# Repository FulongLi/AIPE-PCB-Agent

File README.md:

# AIPE — PCB Agent

AIPE-PCB-Agent is the PCB design automation of the AIPE power-electronics ecosystem. Python generators turn a
requirement file set (specification, insulation table, components, interfaces, floorplan and routing inputs) into
native KiCad 10 projects — hierarchical schematics, placed and grid-routed boards, net classes and design rules —
and run the real `kicad-cli` ERC, DRC and exports with SHA-256 manifests. It sits downstream of
AIPE-Electrical-Design in the AIPE-Workflows pipeline. Its output is an AI-generated engineering prototype for human
review: nothing has been fabricated, energised or measured.

## Features

- Requirement-driven generators (`automation/dab_v1`, `automation/sic_v3`, `automation/kicad_tools`): schematics with
  project libraries, insulation-aware placement, a deterministic grid router with fine-pitch row escapes, pour nets,
  rip-up, time budget and checkpoints.
- Net classes and `.kicad_dru` rules derived from an IEC 60664-1 reference table; values are documented review inputs
  and are never relaxed by the code.
- Native verification: `kicad-cli sch erc`, `pcb drc --schematic-parity --severity-all --refill-zones`, exports
  (Gerber, drill, BOM, placement, STEP, PDF, netlist) with hashed manifests; netlist-equality, routing-quality,
  layout-metric and copper-island checkers.
- Engineering knowledge base (skills, rules, component records) with traceable manufacturer sources.
- Worked examples: SiC buck V1–V3 and the 10 kW dual-active-bridge three-board set DAB-V1.

## Installation

```text
python -m pip install -e ".[test]"          # Python 3.10+; numpy, PyYAML, Shapely, pytest
python -m automation.setup.detect_kicad    # locates an installed KiCad 10 (kicad-cli and its Python); installs nothing
```

## Usage

```text
python -m pytest -q
python -m automation.knowledge.query "recommended layout practices for an isolated SiC gate driver"
python -m automation.dab_v1.pipeline --board primary-power --stages floorplan,copper,route,verify --time-budget 2700
```

The tests run without KiCad (KiCad-dependent tests skip and say so); the pipeline's board stages need KiCad 10.
`--time-budget` time-boxes the router: unrouted nets are reported, the board is still saved and verified.

## Project Information

- Version: 0.1.0 (`pyproject.toml`; first declared version, aligned with `aipe.yaml` schema 0.1.0)
- Status: Prototype. SiC buck V3: two routed boards at zero native ERC/DRC findings. DAB-V1 (re-run of 2026-10-21):
  ERC 0 on all three boards, DRC 0 violations other than unconnected items (18 / 18 / 28 dangling-track warnings),
  26 / 23 / 24 connections still open on primary / secondary / control (from 82 / 81 / 499) - routing candidates, not
  finished boards. No board has been fabricated.
- Developer: Fulong Li
- Organisation: Spirit Connect / AIPE Labs
- License: code — MIT is declared in `aipe.yaml`, but the repository contains no LICENSE file yet (the licence text has
  to be added by the maintainer); KiCad library data under `examples/*/libraries` — CC-BY-SA-4.0 with the KiCad
  library exception (`examples/dab-10kw/control/libraries/LICENSE.md`).

## Documentation

- [Automation architecture](docs/architecture.md), [workflow and acceptance gates](docs/agent-workflow.md),
  [PCB design rules](docs/pcb-design-rules.md), [knowledge system](docs/knowledge-system.md)
- DAB-V1: [example README](examples/dab-10kw/README.md), [architecture review](docs/dab-10kw/architecture-review.md),
  [review report](docs/dab-10kw/review-report.md), [routing remediation](docs/dab-10kw/routing-remediation.md)
- SiC buck examples and milestone history (former README): [docs/history.md](docs/history.md),
  [V3 package](examples/sic-buck-400v-200v-5kw-v3/README.md)
- [Host environment](docs/environment.md), [installation plan](docs/installation-plan.md),
  [CI workflow](.github/workflows/tests.yml)

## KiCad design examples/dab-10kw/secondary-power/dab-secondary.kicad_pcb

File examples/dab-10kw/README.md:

# AIPE 10 kW dual active bridge - DAB-V1 (800 V / 400 V, 100 kHz, SPS)

**AI-GENERATED ENGINEERING PROTOTYPE - HUMAN REVIEW REQUIRED - NOT HARDWARE QUALIFIED.** Three native KiCad 10
projects generated by `automation/dab_v1` from the requirement files in `requirements/`. Clean ERC/DRC results are CAD
statements about the generated files under the recorded rule set; they establish neither electrical safety nor
manufacturability. No fabrication, procurement or energisation is authorised by anything in this directory.

| Deliverable | Location |
|---|---|
| Requirements, assumptions, insulation table, interfaces, floorplans, routing inputs | `requirements/*.yaml`, provenance `requirements/source_manifest.json` |
| Safety-oriented architecture review | [`docs/dab-10kw/architecture-review.md`](../../docs/dab-10kw/architecture-review.md) |
| Review report (what clean ERC/DRC does and does not mean; reviewer checklist) | [`docs/dab-10kw/review-report.md`](../../docs/dab-10kw/review-report.md) |
| Primary power board (800 V bus) | `primary-power/dab-primary.kicad_pro` (schematic `dab-primary.kicad_sch`, board `dab-primary.kicad_pcb`, rules `dab-primary.kicad_dru`, libraries `libraries/`) |
| Secondary power board (400 V bus) | `secondary-power/dab-secondary.kicad_pro` |
| Control board (TMS320F280039C controlCARD) | `control/dab-control.kicad_pro` |
| Design records (evaluated models, groups, spacing evidence, library summaries, schematic mappings) | `design/` |
| Placement and copper plans, routing plans and router reports | `pcb/floorplan_<board>.json`, `pcb/routing_plan_<board>.json`, `pcb/routing_report_<board>.json` |
| Native ERC / DRC manifests (every run, hashed) | `verification/erc/<stamp>/run.json`, `verification/drc/<stamp>/run.json` |
| Netlist equality, routing quality, layout metrics, copper islands, per-board summaries | `verification/circuit_checks/`, `verification/engineering_checks/`, `verification/summary_<board>.json` |
| Manufacturing exports with hashed manifests (Gerbers, drill, BOM, pick-and-place, STEP, PDFs, renders, XML netlist) | `manufacturing/<board>/` |
| Model BOMs | `components/bom_<board>.csv` |

## Reproduction

Host Python 3.10+ (PyYAML optional) and KiCad 10 (kicad-cli and its bundled Python, found by `automation.setup.detect_kicad`).

```text
python -m automation.dab_v1.schematics --board primary-power --erc       # libraries, hierarchical schematic, rules, ERC
<KiCad python> -m automation.dab_v1.floorplan --board primary-power      # placement, copper plan and fine-pitch row escapes (pcbnew)
python -m automation.dab_v1.copper --board primary-power                 # merge the pour rectangles (Shapely)
<KiCad python> -m automation.dab_v1.routing --board primary-power --time-budget 2700   # grid_router.run_plan through PairwiseRouter
python -m automation.dab_v1.verify --board primary-power                 # DRC, exports, netlist equality, quality, layout, islands
python -m automation.dab_v1.pipeline --board primary-power --time-budget 2700          # the stages in sequence
python -m automation.dab_v1.report                                       # refresh the result tables of docs/dab-10kw/review-report.md
python -m automation.dab_v1.provenance                                   # re-fetch and hash the manufacturer sources
python -m pytest tests/test_dab_v1.py -q
```

Repeat with `secondary-power` and `control`. Regeneration reproduces the schematic bytes and the placement; routed
copper is reproduced item for item but not byte for byte (random KiCad item ids), so compare geometry and the hashed
manifests, not file bytes. `--time-budget` (seconds) time-boxes the router: nets it did not reach are recorded as
unresolved with `reason: time_budget`, the board is still poured, filled and saved, and a checkpoint board is written
under `.aipe/dab/checkpoints/` after every router stage. The escape plan of the 0.65 mm rows (same-net bridges, one stub
per run, computed stub lengths) is recorded per IC in `pcb/floorplan_<board>.json -> plan.escape_rows`; see
[`docs/dab-10kw/routing-remediation.md`](../../docs/dab-10kw/routing-remediation.md) for the root causes it addresses.

## What is in the requirement files

- `specification.yaml` - user requirements, engineering assumptions, derived operating point, unverified design
  targets, verification policy.
- `design_constraints.yaml` - stack-ups, minimum features, the IEC 60664-1 reference table (clearance by impulse,
  creepage PD2 MG I, interpolated functional spacing, 8.0 mm reinforced HV-to-SELV), the potential model of the HV
  domains and the router defaults.
- `components.yaml` - every part selection with manufacturer source and the verification level of its pin table or
  envelope.
- `interfaces.yaml` - the 40-way harness map (identical on all three boards), the assumed controlCARD contact map,
  JTAG, CAN, RS-485, auxiliary input, heat-sink NTC and HV terminals.
- `floorplan_<board>.yaml`, `routing_<board>.yaml` - placement geometry and router parameters.

## Status (2026-10-21, remediation run - see `docs/dab-10kw/routing-remediation.md`)

| Board | ERC | Routing | Native DRC (`--schematic-parity --severity-all --refill-zones`) | Exports |
|---|---|---|---|---|
| primary-power | 0 findings | grid router: 2501 tracks, 436 vias, 22 pours, **26 connections left open** (1161 s, time budget not reached) | **0 violations other than unconnected items** (18 dangling-track warnings), **26 unconnected items in 18 nets**, parity 0 | 11 commands, 36 artifacts, hashed |
| secondary-power | 0 findings | 2598 tracks, 449 vias, 21 pours, **23 connections left open** (1189 s) | **0 violations other than unconnected items** (18 dangling-track warnings), **23 unconnected items in 16 nets**, parity 0 | 11 commands, 36 artifacts, hashed |
| control | 0 findings | 3090 tracks, 622 vias, 1 pour, **24 connections left open** (2714 s; the 45-minute budget was reached after one signal trial, rip-up and retry were cut) | **0 violations other than unconnected items** (28 dangling-track warnings), **24 unconnected items in 23 nets**, parity 0 | 11 commands, 36 artifacts, hashed |

Model / schematic netlist / board pad-net equality is exact on all three boards; every power and ground pour is a
single filled island on both power boards; the 8.0 mm HV-to-SELV separation holds on every copper layer and across the
stack (`verification/engineering_checks/barrier_geometry_<board>.json`). The open connections of the power boards are
the narrow nets of the UCC14141 rows (BIAS_ENF, PG_BIAS_N, FBVEE/FBVDD/VEEA/RLIM) and a few island nets; they are listed
per net in `verification/summary_<board>.json` and in the review report. **These are routing candidates, not finished
boards: no Gerber set is manufacturing-ready while connections are open.**

See `docs/dab-10kw/review-report.md` for the per-board ERC/DRC counts, ignored checks, export lists, remaining
violations and the open review items. The controlCARD contact map, several transcribed pin tables, the film-capacitor
and heat-sink envelopes and every insulation value are review inputs, not verified facts.

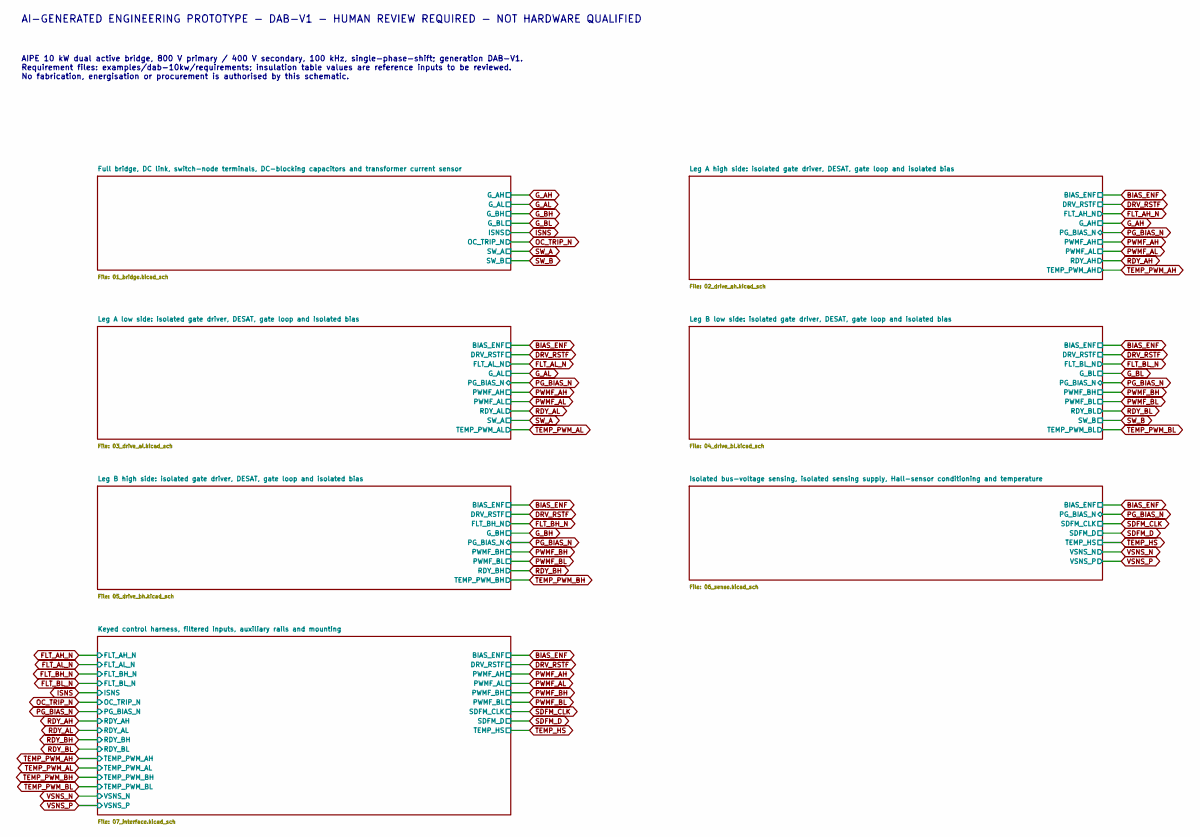
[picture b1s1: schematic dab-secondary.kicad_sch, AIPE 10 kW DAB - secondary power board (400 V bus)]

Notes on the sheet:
AI-GENERATED ENGINEERING PROTOTYPE - DAB-V1 - HUMAN REVIEW REQUIRED - NOT HARDWARE QUALIFIED
AIPE 10 kW dual active bridge, 800 V primary / 400 V secondary, 100 kHz, single-phase-shift; generation DAB-V1. Requirement files: examples/dab-10kw/requirements; insulation table values are reference inputs to be reviewed. No fabrication, energisation or procurement is authorised by this schematic.

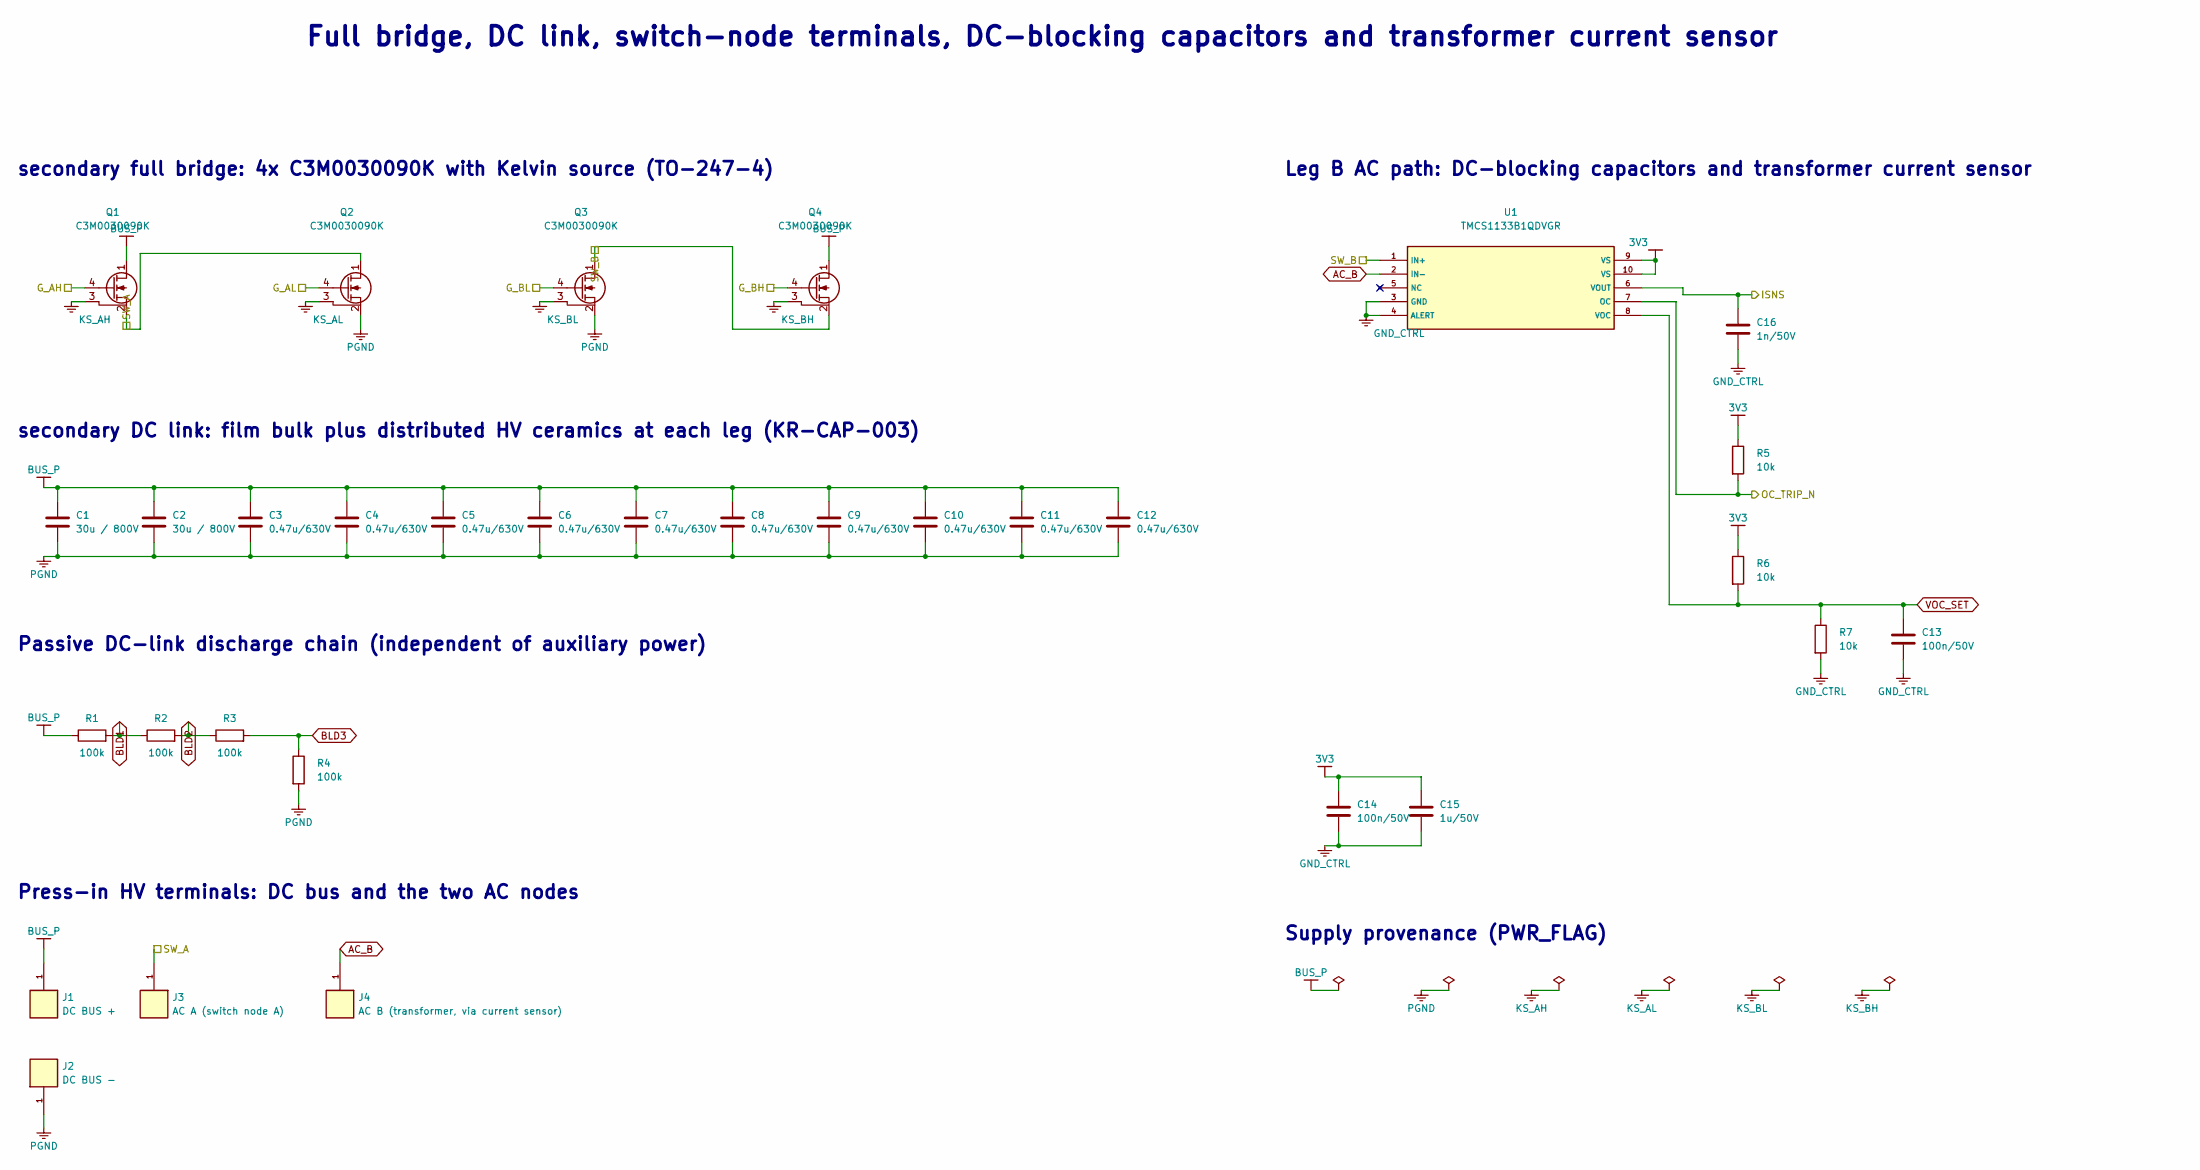
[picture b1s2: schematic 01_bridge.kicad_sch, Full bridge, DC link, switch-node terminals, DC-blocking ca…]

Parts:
C1, C2: 30u / 800V; DAB_FILM_SECONDARY
C3, C4, C5, C6, C7, C8, C9, C10, C11, C12: 0.47u/630V; C_2220_5750Metric
C13, C14: 100n/50V; C_0603_1608Metric
C15: 1u/50V; C_0805_2012Metric
C16: 1n/50V; C_0603_1608Metric
J1: DC BUS +; Wuerth_REDCUBE-THR_WP-THRSH_74651195_THR
J2: DC BUS -; Wuerth_REDCUBE-THR_WP-THRSH_74651195_THR
J3: AC A (switch node A); Wuerth_REDCUBE-THR_WP-THRSH_74651195_THR
J4: AC B (transformer, via current sensor); Wuerth_REDCUBE-THR_WP-THRSH_74651195_THR
Q1, Q2, Q3, Q4: C3M0030090K; TO-247-4_Vertical
R1, R2, R3, R4: 100k; R_1210_3225Metric
R5, R6, R7: 10k; R_0603_1608Metric
U1: TMCS1133B1QDVGR; DAB_TMCS1133_DVG

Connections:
3V3: C14.1, C15.1, R5.1, R6.1, U1.9 (VS), U1.10 (VS); also elsewhere on the board
AC_B: J4.1, U1.2 (IN-)
BLD1: R1.2, R2.1
BLD2: R2.2, R3.1
BLD3: R3.2, R4.1
BUS_P: C1.1, C2.1, C3.1, C4.1, C5.1, C6.1, C7.1, C8.1, C9.1, C10.1, C11.1, C12.1, J1.1, Q1.1 (D), Q4.1 (D), R1.1; also elsewhere on the board
GND_CTRL: C13.2, C14.2, C15.2, C16.2, R7.2, U1.3 (GND), U1.4 (ALERT); also elsewhere on the board
G_AH: Q1.4 (G); also elsewhere on the board
G_AL: Q2.4 (G); also elsewhere on the board
G_BH: Q4.4 (G); also elsewhere on the board
G_BL: Q3.4 (G); also elsewhere on the board
ISNS: C16.1, U1.6 (VOUT); also elsewhere on the board
KS_AH: Q1.3 (KS); also elsewhere on the board
KS_AL: Q2.3 (KS); also elsewhere on the board
KS_BH: Q4.3 (KS); also elsewhere on the board
KS_BL: Q3.3 (KS); also elsewhere on the board
OC_TRIP_N: R5.2, U1.7 (OC); also elsewhere on the board
PGND: C1.2, C2.2, C3.2, C4.2, C5.2, C6.2, C7.2, C8.2, C9.2, C10.2, C11.2, C12.2, J2.1, Q2.2 (S), Q3.2 (S), R4.2; also elsewhere on the board
SW_A: J3.1, Q1.2 (S), Q2.1 (D); also elsewhere on the board
SW_B: Q3.1 (D), Q4.2 (S), U1.1 (IN+); also elsewhere on the board
VOC_SET: C13.1, R6.2, R7.1, U1.8 (VOC)

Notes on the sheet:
Full bridge, DC link, switch-node terminals, DC-blocking capacitors and transformer current sensor
secondary full bridge: 4x C3M0030090K with Kelvin source (TO-247-4)
secondary DC link: film bulk plus distributed HV ceramics at each leg (KR-CAP-003)
Passive DC-link discharge chain (independent of auxiliary power)
Press-in HV terminals: DC bus and the two AC nodes
Leg B AC path: DC-blocking capacitors and transformer current sensor
Supply provenance (PWR_FLAG)

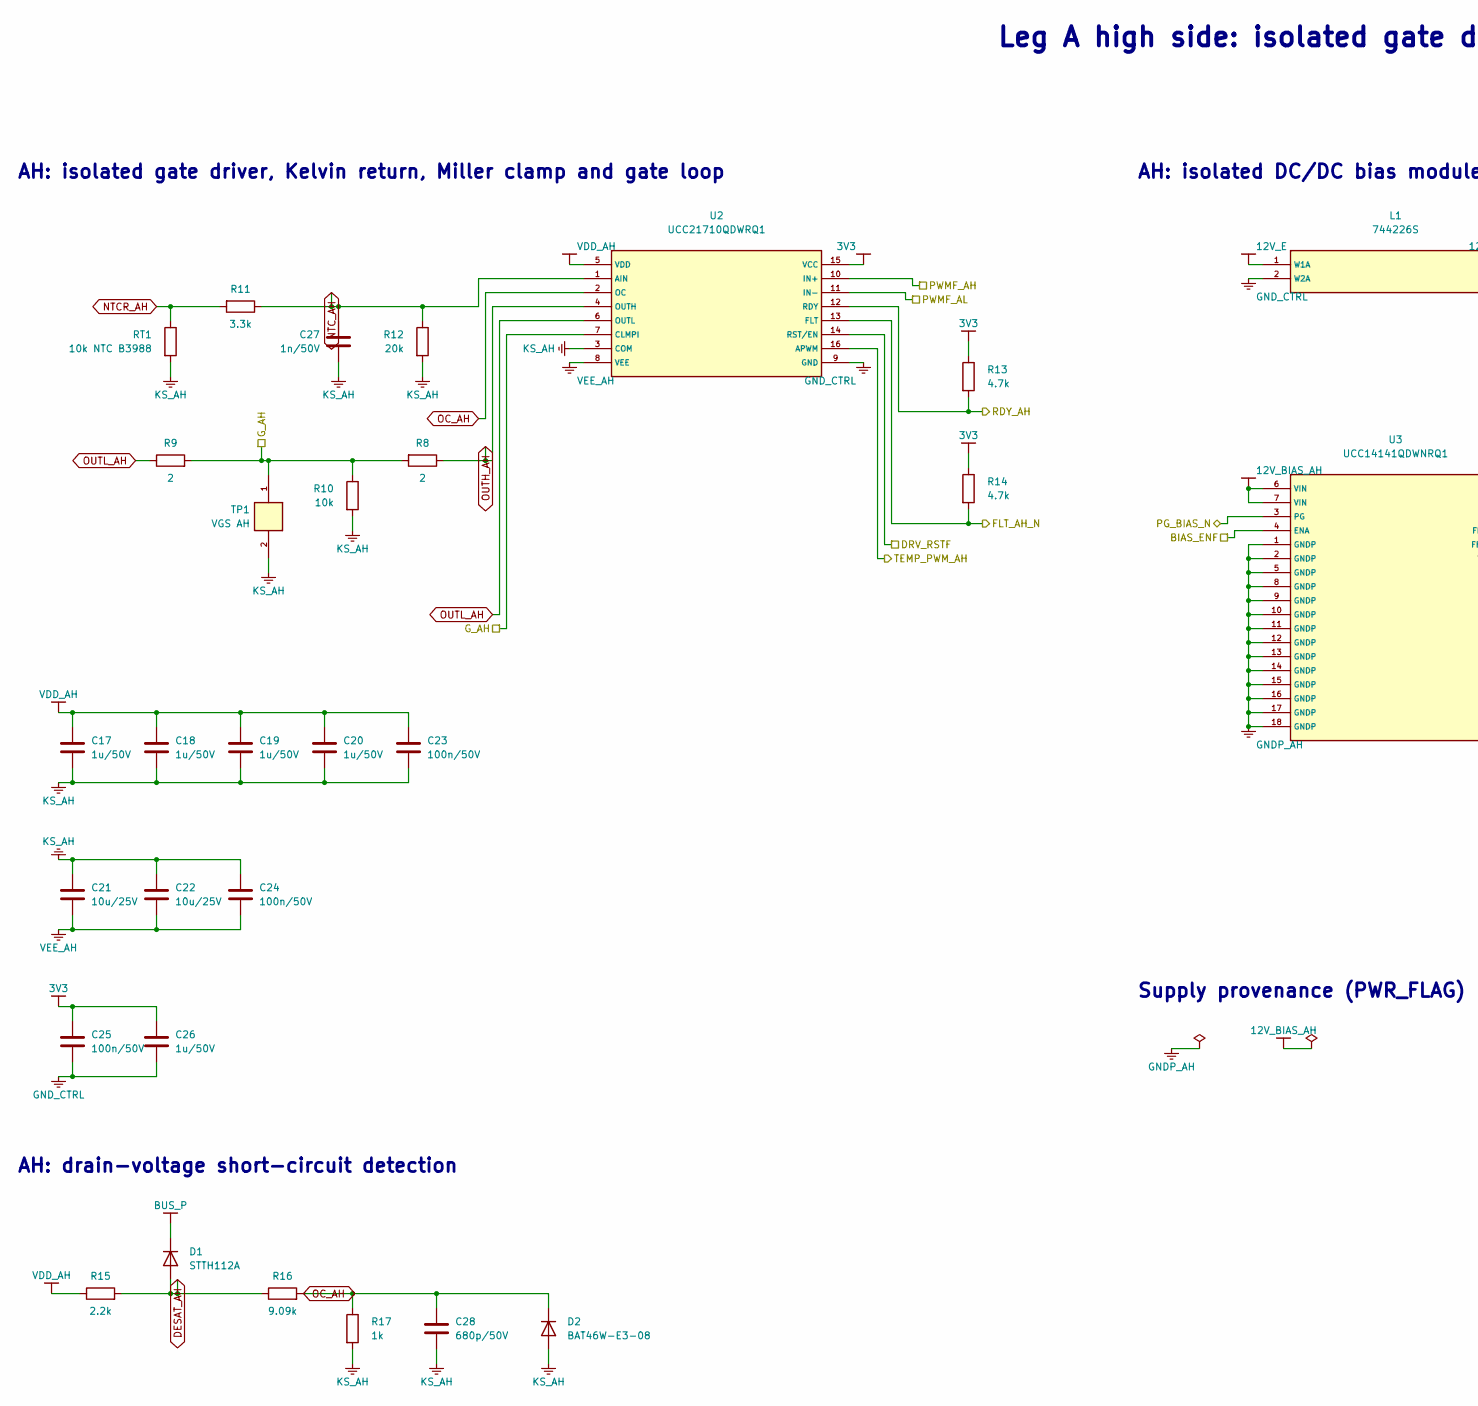
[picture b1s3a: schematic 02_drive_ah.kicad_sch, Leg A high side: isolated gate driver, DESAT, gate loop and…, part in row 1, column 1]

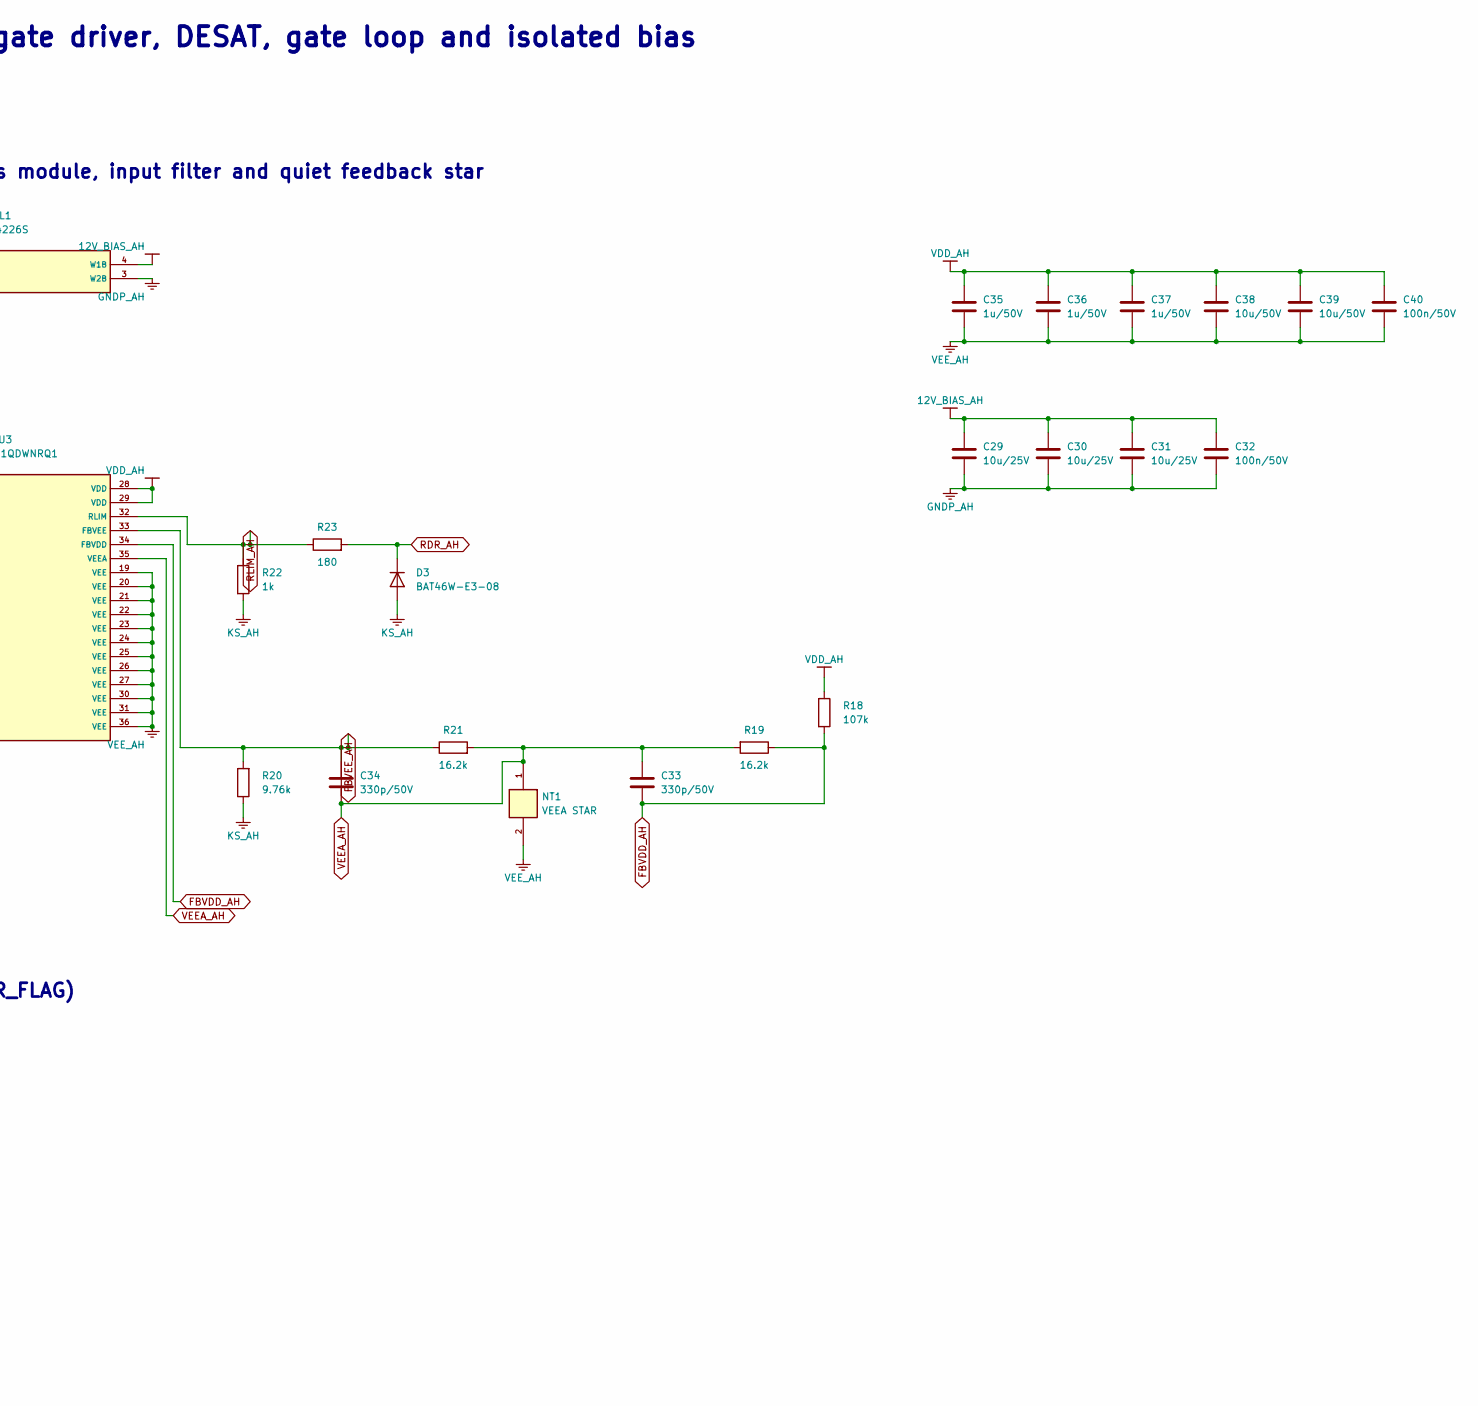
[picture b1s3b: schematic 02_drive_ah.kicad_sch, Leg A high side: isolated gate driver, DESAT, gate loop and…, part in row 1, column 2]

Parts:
C17, C18, C19, C20, C26, C35, C36, C37: 1u/50V; C_0805_2012Metric
C21, C22, C29, C30, C31: 10u/25V; C_1210_3225Metric
C23, C24, C25, C32, C40: 100n/50V; C_0603_1608Metric
C27: 1n/50V; C_0603_1608Metric
C28: 680p/50V; C_0603_1608Metric
C33, C34: 330p/50V; C_0603_1608Metric
C38, C39: 10u/50V; C_1210_3225Metric
D1: STTH112A; D_DO-41_SOD81_P10.16mm_Horizontal
D2, D3: BAT46W-E3-08; D_SOD-123
L1: 744226S; L_CommonMode_Wuerth_WE-SL2
NT1: VEEA STAR; NetTie-2_SMD_Pad0.5mm
R8, R9: 2; R_1206_3216Metric
R10: 10k; R_0805_2012Metric
R11: 3.3k; R_0603_1608Metric
R12: 20k; R_0603_1608Metric
R13, R14: 4.7k; R_0603_1608Metric
R15: 2.2k; R_1206_3216Metric
R16: 9.09k; R_0603_1608Metric
R17: 1k; R_0603_1608Metric
R18: 107k; R_0603_1608Metric
R19, R21: 16.2k; R_0603_1608Metric
R20: 9.76k; R_0603_1608Metric
R22: 1k; R_1206_3216Metric
R23: 180; R_1206_3216Metric
RT1: 10k NTC B3988; R_0805_2012Metric
TP1: VGS AH; TestPoint_2Pads_Pitch2.54mm_Drill0.8mm
U2: UCC21710QDWRQ1; DAB_UCC21710_DW_HV
U3: UCC14141QDWNRQ1; DAB_UCC14141_DWN

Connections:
3V3: C25.1, C26.1, R13.1, R14.1, U2.15 (VCC); also elsewhere on the board
12V_BIAS_AH: C29.1, C30.1, C31.1, C32.1, L1.4 (W1B), U3.6 (VIN), U3.7 (VIN)
12V_E: L1.1 (W1A); also elsewhere on the board
BIAS_ENF: U3.4 (ENA); also elsewhere on the board
BUS_P: D1.1 (K); also elsewhere on the board
DESAT_AH: D1.2 (A), R15.2, R16.1
DRV_RSTF: U2.14 (RST/EN); also elsewhere on the board
FBVDD_AH: C33.1, R18.2, R19.1, U3.34 (FBVDD)
FBVEE_AH: C34.1, R20.2, R21.1, U3.33 (FBVEE)
FLT_AH_N: R14.2, U2.13 (FLT); also elsewhere on the board
GNDP_AH: C29.2, C30.2, C31.2, C32.2, L1.3 (W2B), U3.1 (GNDP), U3.2 (GNDP), U3.5 (GNDP), U3.8 (GNDP), U3.9 (GNDP), U3.10 (GNDP), U3.11 (GNDP), U3.12 (GNDP), U3.13 (GNDP), U3.14 (GNDP), U3.15 (GNDP), U3.16 (GNDP), U3.17 (GNDP), U3.18 (GNDP)
GND_CTRL: C25.2, C26.2, L1.2 (W2A), U2.9 (GND); also elsewhere on the board
G_AH: R8.2, R9.2, R10.1, TP1.1, U2.7 (CLMPI); also elsewhere on the board
KS_AH: C17.2, C18.2, C19.2, C20.2, C21.1, C22.1, C23.2, C24.1, C27.2, C28.2, D2.2 (A), D3.2 (A), R10.2, R12.2, R17.2, R20.1, R22.2, RT1.2, TP1.2, U2.3 (COM); also elsewhere on the board
NTCR_AH: R11.2, RT1.1
NTC_AH: C27.1, R11.1, R12.1, U2.1 (AIN)
OC_AH: C28.1, D2.1 (K), R16.2, R17.1, U2.2 (OC)
OUTH_AH: R8.1, U2.4 (OUTH)
OUTL_AH: R9.1, U2.6 (OUTL)
PG_BIAS_N: U3.3 (PG); also elsewhere on the board
PWMF_AH: U2.10 (IN+); also elsewhere on the board
PWMF_AL: U2.11 (IN-); also elsewhere on the board
RDR_AH: D3.1 (K), R23.2
RDY_AH: R13.2, U2.12 (RDY); also elsewhere on the board
RLIM_AH: R22.1, R23.1, U3.32 (RLIM)
TEMP_PWM_AH: U2.16 (APWM); also elsewhere on the board
VDD_AH: C17.1, C18.1, C19.1, C20.1, C23.1, C35.1, C36.1, C37.1, C38.1, C39.1, C40.1, R15.1, R18.1, U2.5 (VDD), U3.28 (VDD), U3.29 (VDD)
VEEA_AH: C33.2, C34.2, NT1.1, R19.2, R21.2, U3.35 (VEEA)
VEE_AH: C21.2, C22.2, C24.2, C35.2, C36.2, C37.2, C38.2, C39.2, C40.2, NT1.2, U2.8 (VEE), U3.19 (VEE), U3.20 (VEE), U3.21 (VEE), U3.22 (VEE), U3.23 (VEE), U3.24 (VEE), U3.25 (VEE), U3.26 (VEE), U3.27 (VEE), U3.30 (VEE), U3.31 (VEE), U3.36 (VEE)

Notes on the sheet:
Leg A high side: isolated gate driver, DESAT, gate loop and isolated bias
AH: isolated gate driver, Kelvin return, Miller clamp and gate loop
AH: drain-voltage short-circuit detection
AH: isolated DC/DC bias module, input filter and quiet feedback star
Supply provenance (PWR_FLAG)

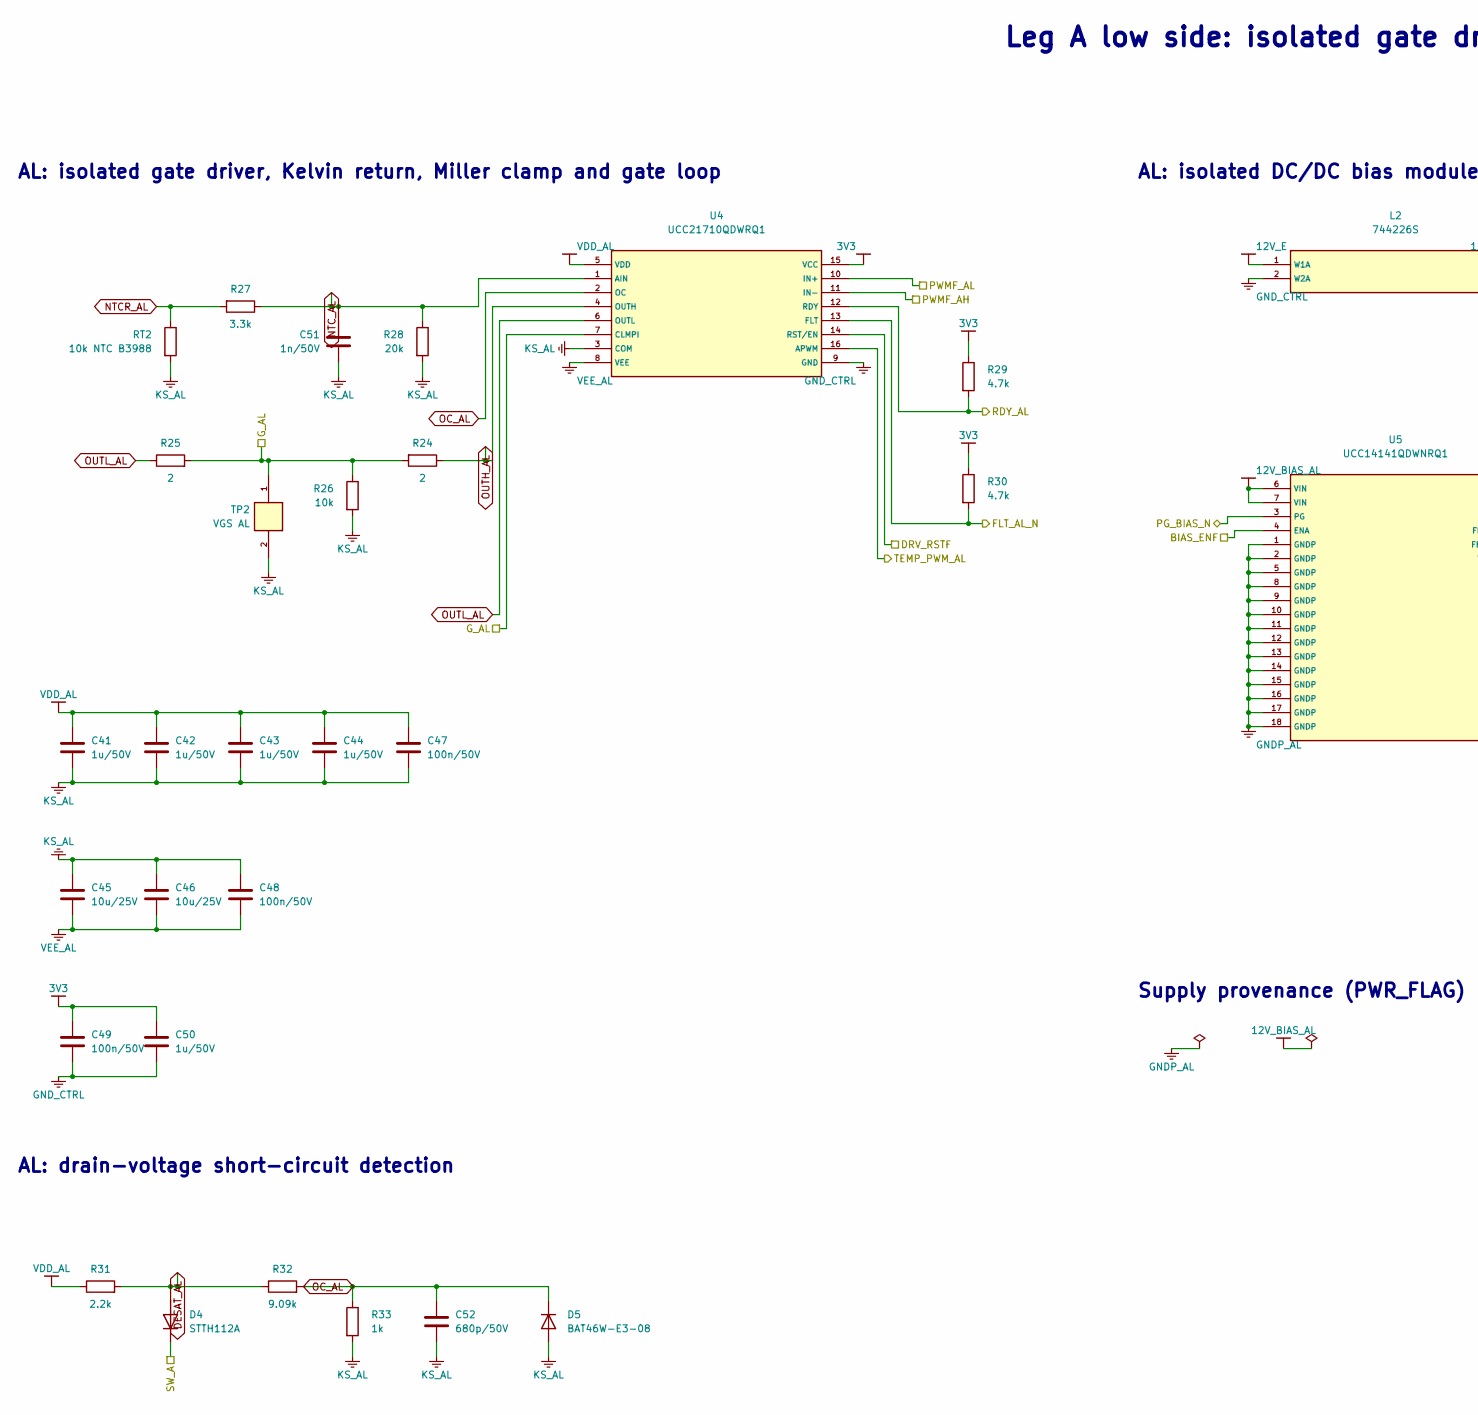
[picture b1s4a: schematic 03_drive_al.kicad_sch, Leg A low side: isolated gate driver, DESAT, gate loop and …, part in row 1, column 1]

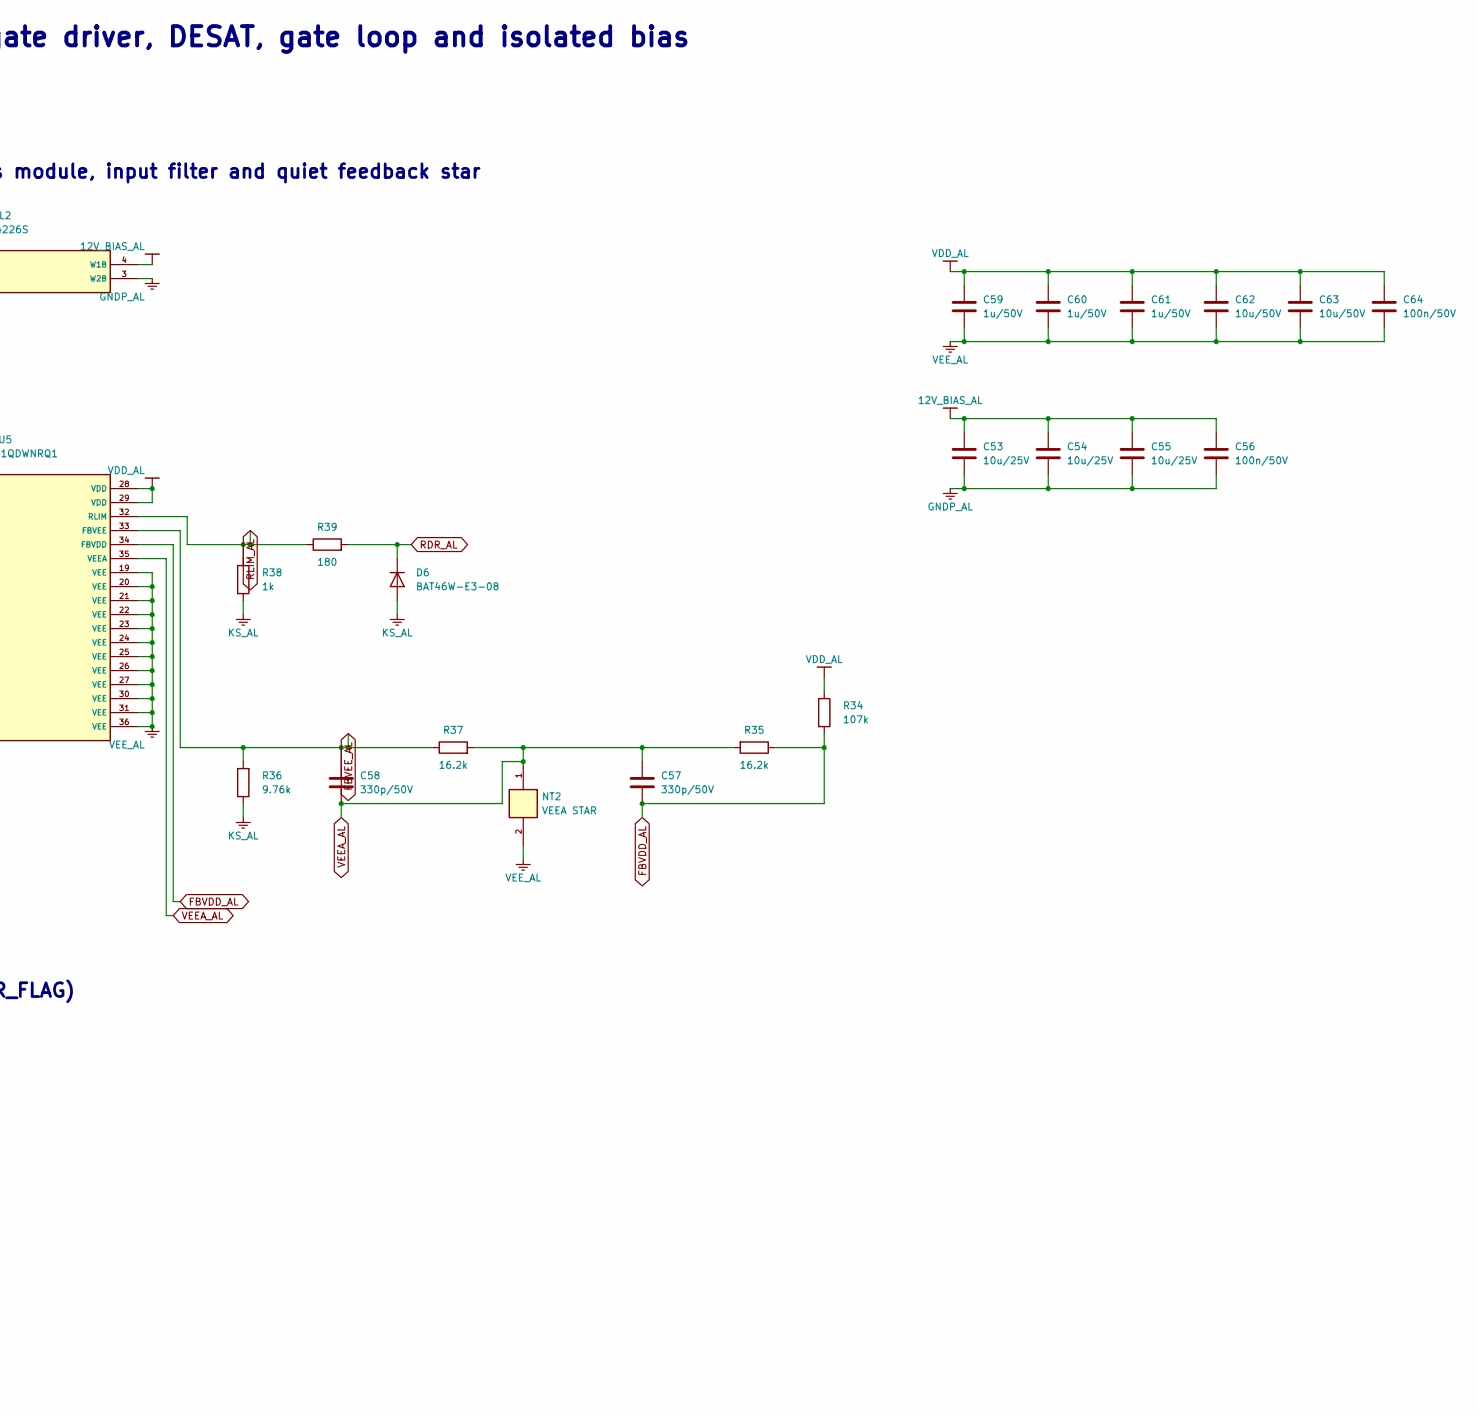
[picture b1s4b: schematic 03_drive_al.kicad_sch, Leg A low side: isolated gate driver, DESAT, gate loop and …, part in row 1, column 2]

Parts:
C41, C42, C43, C44, C50, C59, C60, C61: 1u/50V; C_0805_2012Metric
C45, C46, C53, C54, C55: 10u/25V; C_1210_3225Metric
C47, C48, C49, C56, C64: 100n/50V; C_0603_1608Metric
C51: 1n/50V; C_0603_1608Metric
C52: 680p/50V; C_0603_1608Metric
C57, C58: 330p/50V; C_0603_1608Metric
C62, C63: 10u/50V; C_1210_3225Metric
D4: STTH112A; D_DO-41_SOD81_P10.16mm_Horizontal
D5, D6: BAT46W-E3-08; D_SOD-123
L2: 744226S; L_CommonMode_Wuerth_WE-SL2
NT2: VEEA STAR; NetTie-2_SMD_Pad0.5mm
R24, R25: 2; R_1206_3216Metric
R26: 10k; R_0805_2012Metric
R27: 3.3k; R_0603_1608Metric
R28: 20k; R_0603_1608Metric
R29, R30: 4.7k; R_0603_1608Metric
R31: 2.2k; R_1206_3216Metric
R32: 9.09k; R_0603_1608Metric
R33: 1k; R_0603_1608Metric
R34: 107k; R_0603_1608Metric
R35, R37: 16.2k; R_0603_1608Metric
R36: 9.76k; R_0603_1608Metric
R38: 1k; R_1206_3216Metric
R39: 180; R_1206_3216Metric
RT2: 10k NTC B3988; R_0805_2012Metric
TP2: VGS AL; TestPoint_2Pads_Pitch2.54mm_Drill0.8mm
U4: UCC21710QDWRQ1; DAB_UCC21710_DW_HV
U5: UCC14141QDWNRQ1; DAB_UCC14141_DWN

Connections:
3V3: C49.1, C50.1, R29.1, R30.1, U4.15 (VCC); also elsewhere on the board
12V_BIAS_AL: C53.1, C54.1, C55.1, C56.1, L2.4 (W1B), U5.6 (VIN), U5.7 (VIN)
12V_E: L2.1 (W1A); also elsewhere on the board
BIAS_ENF: U5.4 (ENA); also elsewhere on the board
DESAT_AL: D4.2 (A), R31.2, R32.1
DRV_RSTF: U4.14 (RST/EN); also elsewhere on the board
FBVDD_AL: C57.1, R34.2, R35.1, U5.34 (FBVDD)
FBVEE_AL: C58.1, R36.2, R37.1, U5.33 (FBVEE)
FLT_AL_N: R30.2, U4.13 (FLT); also elsewhere on the board
GNDP_AL: C53.2, C54.2, C55.2, C56.2, L2.3 (W2B), U5.1 (GNDP), U5.2 (GNDP), U5.5 (GNDP), U5.8 (GNDP), U5.9 (GNDP), U5.10 (GNDP), U5.11 (GNDP), U5.12 (GNDP), U5.13 (GNDP), U5.14 (GNDP), U5.15 (GNDP), U5.16 (GNDP), U5.17 (GNDP), U5.18 (GNDP)
GND_CTRL: C49.2, C50.2, L2.2 (W2A), U4.9 (GND); also elsewhere on the board
G_AL: R24.2, R25.2, R26.1, TP2.1, U4.7 (CLMPI); also elsewhere on the board
KS_AL: C41.2, C42.2, C43.2, C44.2, C45.1, C46.1, C47.2, C48.1, C51.2, C52.2, D5.2 (A), D6.2 (A), R26.2, R28.2, R33.2, R36.1, R38.2, RT2.2, TP2.2, U4.3 (COM); also elsewhere on the board
NTCR_AL: R27.2, RT2.1
NTC_AL: C51.1, R27.1, R28.1, U4.1 (AIN)
OC_AL: C52.1, D5.1 (K), R32.2, R33.1, U4.2 (OC)
OUTH_AL: R24.1, U4.4 (OUTH)
OUTL_AL: R25.1, U4.6 (OUTL)
PG_BIAS_N: U5.3 (PG); also elsewhere on the board
PWMF_AH: U4.11 (IN-); also elsewhere on the board
PWMF_AL: U4.10 (IN+); also elsewhere on the board
RDR_AL: D6.1 (K), R39.2
RDY_AL: R29.2, U4.12 (RDY); also elsewhere on the board
RLIM_AL: R38.1, R39.1, U5.32 (RLIM)
SW_A: D4.1 (K); also elsewhere on the board
TEMP_PWM_AL: U4.16 (APWM); also elsewhere on the board
VDD_AL: C41.1, C42.1, C43.1, C44.1, C47.1, C59.1, C60.1, C61.1, C62.1, C63.1, C64.1, R31.1, R34.1, U4.5 (VDD), U5.28 (VDD), U5.29 (VDD)
VEEA_AL: C57.2, C58.2, NT2.1, R35.2, R37.2, U5.35 (VEEA)
VEE_AL: C45.2, C46.2, C48.2, C59.2, C60.2, C61.2, C62.2, C63.2, C64.2, NT2.2, U4.8 (VEE), U5.19 (VEE), U5.20 (VEE), U5.21 (VEE), U5.22 (VEE), U5.23 (VEE), U5.24 (VEE), U5.25 (VEE), U5.26 (VEE), U5.27 (VEE), U5.30 (VEE), U5.31 (VEE), U5.36 (VEE)

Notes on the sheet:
Leg A low side: isolated gate driver, DESAT, gate loop and isolated bias
AL: isolated gate driver, Kelvin return, Miller clamp and gate loop
AL: drain-voltage short-circuit detection
AL: isolated DC/DC bias module, input filter and quiet feedback star
Supply provenance (PWR_FLAG)
